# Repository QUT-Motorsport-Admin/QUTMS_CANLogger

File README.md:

# BMS CAN Data Logger

This repository is for the continued development of the CAN data logger for BMS-Vehicle communication.

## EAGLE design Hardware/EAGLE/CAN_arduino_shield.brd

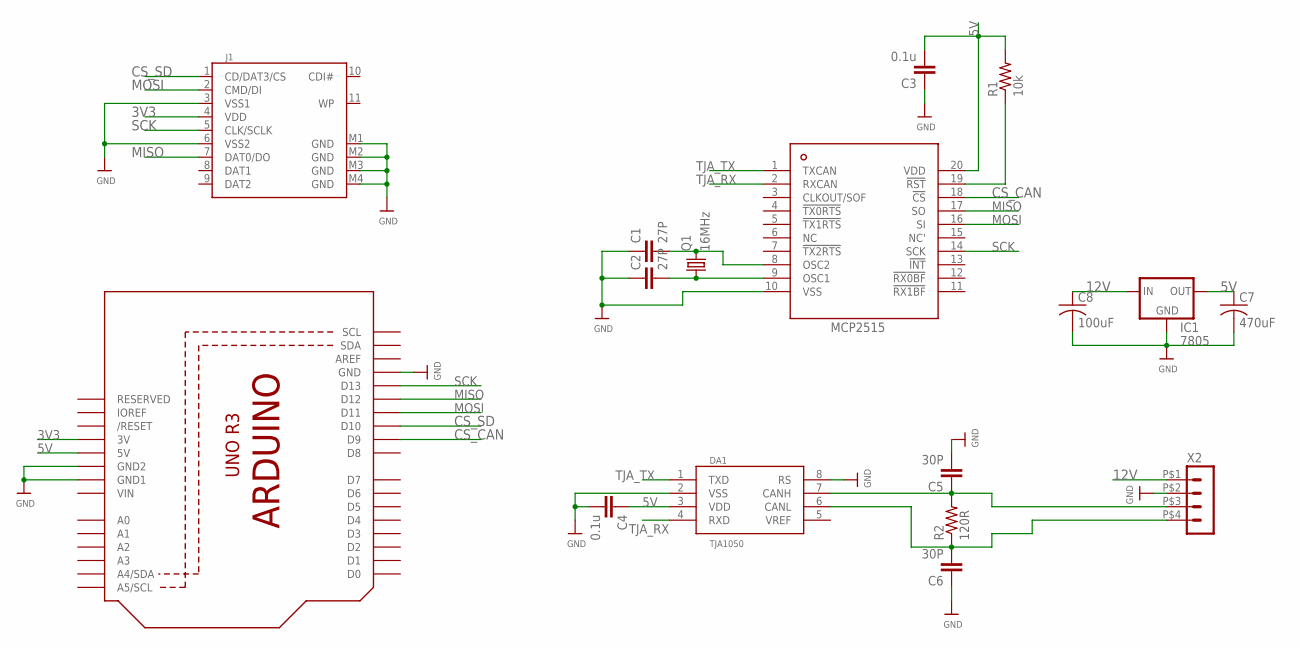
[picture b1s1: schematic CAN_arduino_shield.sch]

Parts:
C1, C2: 27P; C0805
C3, C4: 0.1u; C0805
C5, C6: 30P; C0805
C7: 470uF; C025-050X050
C8: 100uF; C025-050X050
DA1: TJA1050; SO08
IC1: 7805; 78XXS
J1: SDCARD; SDCMF-10915W010
Q1: 16MHz; HC49/S
R1: 10k; M0805
R2: 120R; M0805
U1: ARDUINOR3-BPLACE
U$1: MCP2515; TSSOP20
X2: HEADER_POS4_43045-0412; 43045-0412

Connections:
3V3: J1.4 (VDD), U1.3V
5V: C3.2, C4.1, C7.1, DA1.3 (VDD), IC1.OUT, R1.2, U1.5V, U$1.20 (VDD)
12V: C8.1, IC1.IN, X2.P$1 (1)
CS_CAN: U1.D9, U$1.18 (!CS)
CS_SD: J1.1 (CD/DAT3/CS), U1.D10
GND: C1.1, C2.1, C3.1, C4.2, C5.2, C6.1, C7.2, C8.2, DA1.2 (VSS), DA1.8 (RS), IC1.GND, J1.3 (VSS1), J1.6 (VSS2), J1.M1 (GND), J1.M2 (GND), J1.M3 (GND), J1.M4 (GND), U1.GND, U1.GND1, U1.GND2, U$1.10 (VSS), X2.P$2 (2)
MISO: J1.7 (DAT0/DO), U1.D12, U$1.17 (SO)
MOSI: J1.2 (CMD/DI), U1.D11, U$1.16 (SI)
unnamed: C1.2, Q1.2, U$1.8 (OSC2)
unnamed: C2.2, Q1.1, U$1.9 (OSC1)
unnamed: C5.1, DA1.7 (CANH), R2.2, X2.P$3 (3)
unnamed: C6.2, DA1.6 (CANL), R2.1, X2.P$4 (4)
unnamed: R1.1, U$1.19 (!RST)
SCK: J1.5 (CLK/SCLK), U1.D13, U$1.14 (SCK)
TJA_RX: DA1.4 (RXD), U$1.2 (RXCAN)
TJA_TX: DA1.1 (TXD), U$1.1 (TXCAN)
VIN: U1.VIN

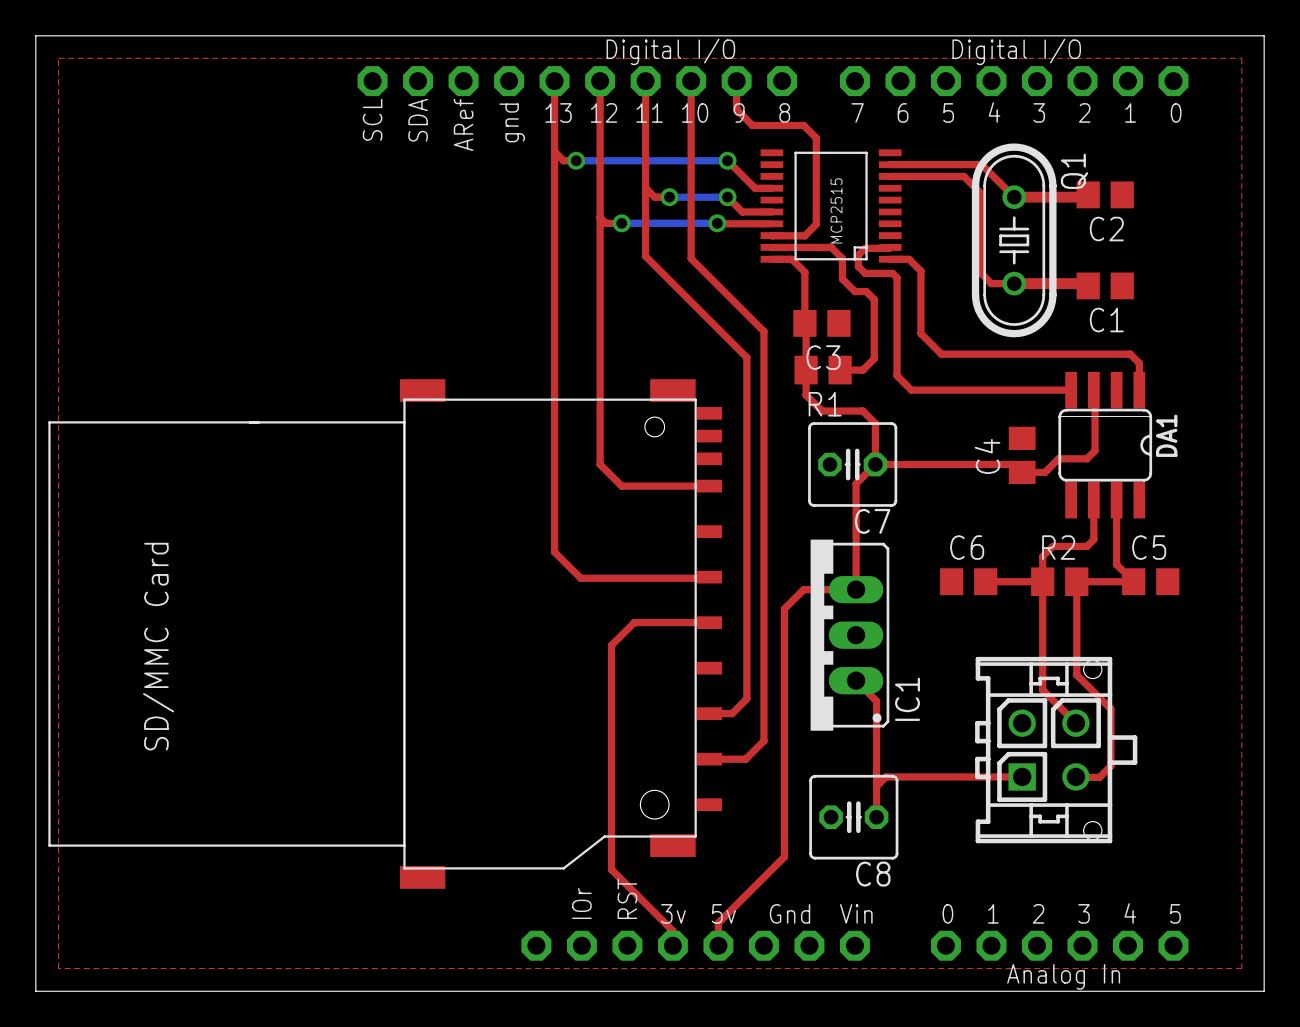
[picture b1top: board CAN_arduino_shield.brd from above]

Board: 2 copper layers, 68.4 x 53.2 mm, 17 parts (0 on the bottom side), 16 nets.

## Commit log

2019-06-23 Version 1 of the CAN logger

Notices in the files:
parts and their libraries:
microbuilder: This work is placed in the public domain, and may be freely used for commercial and non-commercial work with the following conditions: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
